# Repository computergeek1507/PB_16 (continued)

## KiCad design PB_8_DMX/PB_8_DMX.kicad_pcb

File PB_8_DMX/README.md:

# Copyright and Disclaimer
Copyright: Scott Hanson

This documentation describes Open Hardware and is licensed under the CERN Open Hardware License Version 2 - Strongly Reciprocal. (CERN-OHL-S)

You may redistribute and modify this documentation under the terms of the CERN OHL-S-v2 (https://ohwr.org/cern_ohl_s_v2.txt). This documentation is distributed WITHOUT ANY EXPRESS OR IMPLIED WARRANTY, INCLUDING OF MERCHANTABILITY, SATISFACTORY QUALITY AND FITNESS FOR A PARTICULAR PURPOSE. Please see the CERN OHL v2-S for applicable conditions

**Under CERN OHL-S-v2, derivative work must be publicly released as defined in subsection 3.3**

# PB 8 DMX

The PB 8 DMX Controller is designed as an open source DIY hobbyist controller. A Pocketbeagle running FPP drives the 8 serial ports. The design was made with all through hole components for easy assembly by most users. It is designed to be modular and support many use cases. It runs a full Linux operating system with ethernet, WIFI and audio supported over the USB port. It can run in standalone, or be used with other controllers/devices. It is 140mm (5’) wide by 103mm(4’) tall. The controllers small form factor and simplistic design are intended to limit overall cost. All the design files are open source and available on github. Open source applications were used to create this controller. [KiCad](http://kicad.org/) was used for the PCB design, and [LibreOffice](https://www.libreoffice.org/) for the documentation.

To order your own PCB upload the gerber.zip file to your favorite PCB manufacture of choice, I personally use [jlcpcb.com](https://jlcpcb.com/).

### Features
* Powered by FPP Falcon Player
* Standalone/Master/Remote/Bridge Support
* 8 DMX Serial Outputs
* USB port for Ethernet,WIFI, or Audio
* OLED Display header
* Adafruit Real Time Clock Header Connector
* 2 pin GPIO Header for Push Button or Relay Support
* 5v - 24v Vin Support

## [Gerbers](https://github.com/computergeek1507/PB_16/raw/master/jlcpcb/production_files/GERBER-PB_8_DMX.zip)

## [Interactive BOM](https://computergeek1507.github.io/PB_16/PB_8_DMX/bom/ibom)

---
## Changelog

v1
-
* 2023-09-24
* Initial Version.

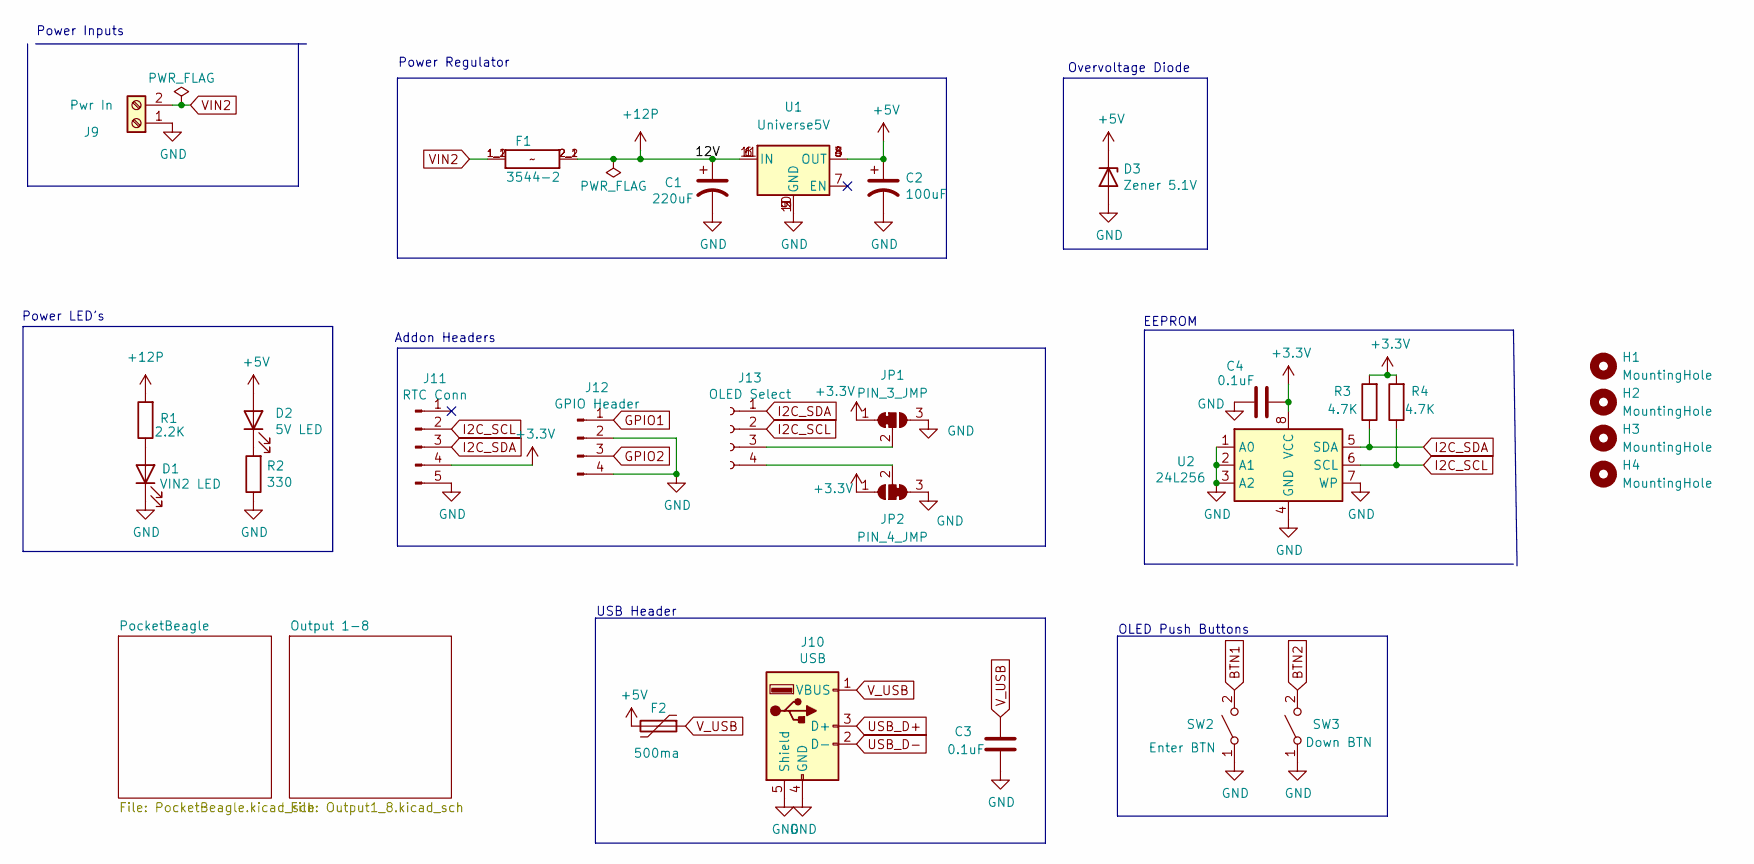
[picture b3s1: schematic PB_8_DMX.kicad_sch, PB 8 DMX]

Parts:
C1: 220uF; CP_Radial_D10.0mm_P5.00mm; MPN ECA-1HM221; Digi-Key_PN P5183-ND
C2: 100uF; CP_Radial_D5.0mm_P2.00mm; MPN 16ZLH100MEFC5X11; Digi-Key_PN 1189-1148-ND
C3, C4: 0.1uF; C_Rect_L7.0mm_W2.0mm_P5.00mm; MPN SR215C104KARTR1; Digi-Key_PN 478-7336-1-ND
D1: VIN2 LED; LED_D3.0mm_Clear; MPN WP3A8GD; Digi-Key_PN 754-1217-ND
D2: 5V LED; LED_D3.0mm_Clear; MPN WP3A8GD; Digi-Key_PN 754-1217-ND
D3: Zener 5.1V; D_5W_P10.16mm_Horizontal; MPN 1N5338BRLG; Digi-Key_PN 1N5338BRLGOSCT-ND
F1: 3544-2; FUSE_3544-2; MPN 3544-2; Digi-Key_PN 36-3544-2-ND
F2: 500ma; Fuse_BelFuse_0ZRE0005FF_L8.3mm_W3.8mm; MPN RXEF050-2; Digi-Key_PN RXEF050-2HFCT-ND
H1, H2, H3, H4: MountingHole; MountingHole_3.7mm
J9: Pwr In; TerminalBlock_Phoenix_MKDS-1,5-2_1x02_P5.00mm_Horizontal; MPN 1727010; Digi-Key_PN 277-1947-ND
J10: USB; USB_A_Molex_105057_Vertical; MPN 1050570001; Digi-Key_PN WM8672-ND
J11: RTC Conn; PinHeader_1x05_P2.54mm_Vertical; MPN 61300511121; Digi-Key_PN 732-5318-ND
J12: GPIO Header; JST_XH_B4B-XH-A_1x04_P2.50mm_Vertical; MPN B4B-XH-A(LF)(SN); Digi-Key_PN 455-2249-ND
J13: OLED Select; PinSocket_1x04_P2.54mm_Vertical; MPN PPTC041LFBN-RC; Digi-Key_PN S7002-ND
JP1: PIN_3_JMP; SolderJumper-3_P1mm_Bridged12
JP2: PIN_4_JMP; SolderJumper-3_P1mm_Bridged23
R1: 2.2K; R_Axial_DIN0207_L6.3mm_D2.5mm_P7.62mm_Horizontal; MPN CF14JT2K20; Digi-Key_PN CF14JT2K20CT-ND
R2: 330; R_Axial_DIN0207_L6.3mm_D2.5mm_P7.62mm_Horizontal; MPN CF14JT330R; Digi-Key_PN CF14JT330RCT-ND
R3, R4: 4.7K; R_Axial_DIN0207_L6.3mm_D2.5mm_P7.62mm_Horizontal; MPN CF14JT4K70; Digi-Key_PN CF14JT4K70CT-ND
SW2: Enter BTN; SW_PUSH_6mm; MPN 1825910-6; Digi-Key_PN 450-1650-ND
SW3: Down BTN; SW_PUSH_6mm; MPN 1825910-6; Digi-Key_PN 450-1650-ND
U1: Universe5V; Universal_5V_Horizontal; MPN OKI-78SR-5/1.5-W36-C; Digi-Key_PN 811-2196-5-ND
U2: 24L256; DIP-8_W7.62mm; MPN FT24C256A-UDR-B; Digi-Key_PN 1219-1052-ND

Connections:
+3.3V: C4.1, J11.4, JP1.1 (A), JP2.1 (A), R3.2, R4.2, U2.8 (VCC); also elsewhere on the board
+5V: C2.1, D2.2 (A), D3.1 (K), F2.2, U1.3 (OUT), U1.4 (OUT), U1.8 (OUT); also elsewhere on the board
+12P: C1.1, F1.2_1 (2), F1.2_2 (2), R1.2, U1.1 (IN), U1.6 (IN), U1.11 (IN)
BTN1: SW2.2 (B); also elsewhere on the board
BTN2: SW3.2 (B); also elsewhere on the board
GND: C1.2, C2.2, C3.2, C4.2, D1.1 (K), D3.2 (A), J9.1, J10.4 (GND), J10.5 (Shield), J11.5, J12.2, J12.4, JP1.3 (B), JP2.3 (B), R2.1, SW2.1 (A), SW3.1 (A), U1.2 (GND), U1.5 (GND), U1.9 (GND), U1.10 (GND), U2.1 (A0), U2.2 (A1), U2.3 (A2), U2.4 (GND), U2.7 (WP); also elsewhere on the board
GPIO1: J12.1; also elsewhere on the board
GPIO2: J12.3; also elsewhere on the board
I2C_SCL: J11.2, J13.2, R4.1, U2.6 (SCL); also elsewhere on the board
I2C_SDA: J11.3, J13.1, R3.1, U2.5 (SDA); also elsewhere on the board
unnamed: D1.2 (A), R1.1
unnamed: D2.1 (K), R2.2
unnamed: J13.3, JP1.2 (C)
unnamed: J13.4, JP2.2 (C)
USB_D+: J10.3 (D+); also elsewhere on the board
USB_D-: J10.2 (D-); also elsewhere on the board
VIN2: F1.1_1 (1), F1.1_2 (1), J9.2
V_USB: C3.1, F2.1, J10.1 (VBUS); also elsewhere on the board

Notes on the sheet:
Overvoltage Diode
EEPROM
USB Header
OLED Push Buttons
Addon Headers
Power Regulator
Power LED's
Power Inputs

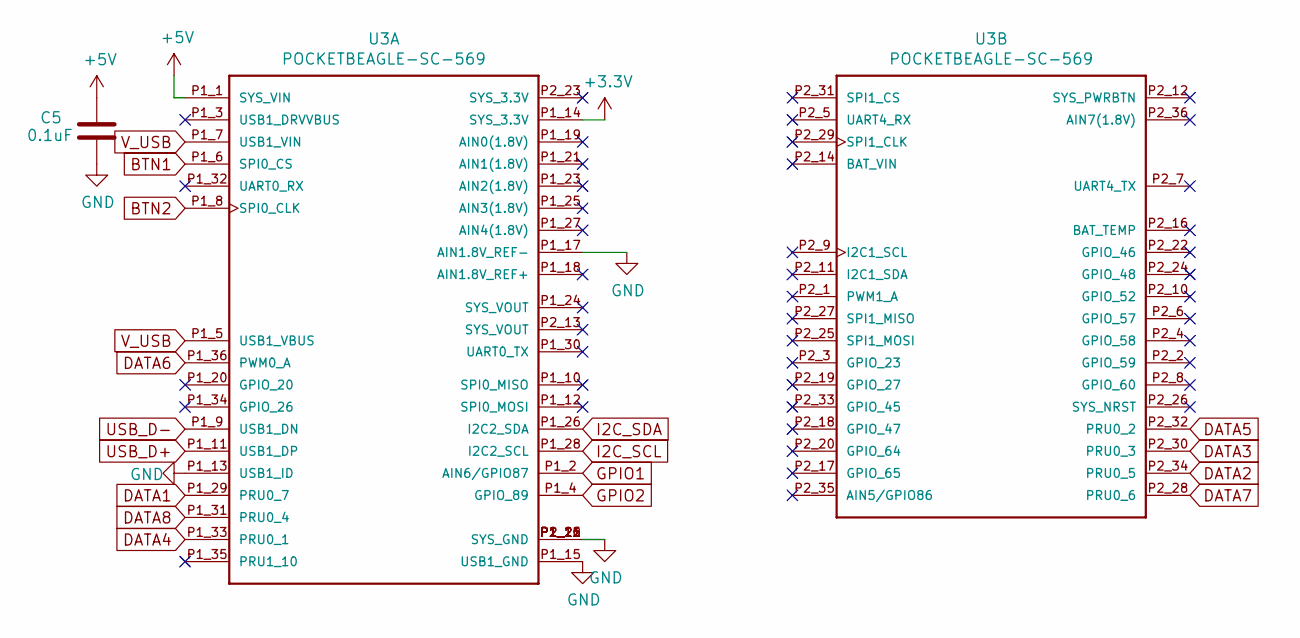
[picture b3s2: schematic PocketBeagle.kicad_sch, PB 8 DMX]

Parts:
C5: 0.1uF; C_Rect_L7.0mm_W2.0mm_P5.00mm; MPN SR215C104KARTR1; Digi-Key_PN 478-7336-1-ND
U3: POCKETBEAGLE-SC-569; BEAGLE_POCKETBEAGLE-SC-569; MPN POCKETBEAGLE-SC-569; Digi-Key_PN POCKETBEAGLE-SC-569-ND

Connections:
+3.3V: U3.P1_14 (SYS_3.3V); also elsewhere on the board
+5V: C5.1, U3.P1_1 (SYS_VIN); also elsewhere on the board
BTN1: U3.P1_6 (SPI0_CS); also elsewhere on the board
BTN2: U3.P1_8 (SPI0_CLK); also elsewhere on the board
DATA1: U3.P1_29 (PRU0_7); also elsewhere on the board
DATA2: U3.P2_34 (PRU0_5); also elsewhere on the board
DATA3: U3.P2_30 (PRU0_3); also elsewhere on the board
DATA4: U3.P1_33 (PRU0_1); also elsewhere on the board
DATA5: U3.P2_32 (PRU0_2); also elsewhere on the board
DATA6: U3.P1_36 (PWM0_A); also elsewhere on the board
DATA7: U3.P2_28 (PRU0_6); also elsewhere on the board
DATA8: U3.P1_31 (PRU0_4); also elsewhere on the board
GND: C5.2, U3.P1_13 (USB1_ID), U3.P1_15 (USB1_GND), U3.P1_16 (SYS_GND), U3.P1_17 (AIN1.8V_REF-), U3.P1_22 (SYS_GND), U3.P2_15 (SYS_GND), U3.P2_21 (SYS_GND); also elsewhere on the board
GPIO1: U3.P1_2 (AIN6/GPIO87); also elsewhere on the board
GPIO2: U3.P1_4 (GPIO_89); also elsewhere on the board
I2C_SCL: U3.P1_28 (I2C2_SCL); also elsewhere on the board
I2C_SDA: U3.P1_26 (I2C2_SDA); also elsewhere on the board
USB_D+: U3.P1_11 (USB1_DP); also elsewhere on the board
USB_D-: U3.P1_9 (USB1_DN); also elsewhere on the board
V_USB: U3.P1_5 (USB1_VBUS), U3.P1_7 (USB1_VIN); also elsewhere on the board

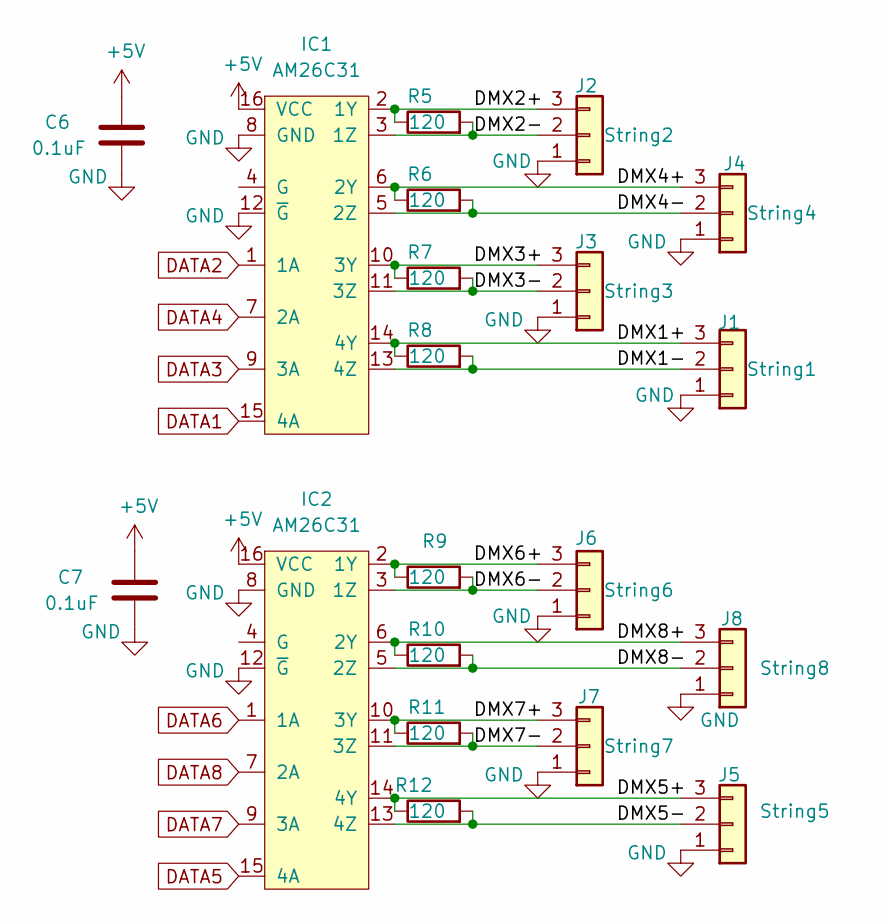
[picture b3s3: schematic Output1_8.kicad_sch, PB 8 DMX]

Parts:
C6, C7: 0.1uF; C_Rect_L7.0mm_W2.0mm_P5.00mm; MPN SR215C104KARTR1; Digi-Key_PN 478-7336-1-ND
IC1, IC2: AM26C31; DIP-16_W7.62mm; MPN 4975637; Farnell 4975637
J1: String1; PhoenixContact_MCV_1,5_3-G-3.5_1x03_P3.50mm_Vertical; MPN 1843619/OSTTJ0311530; Digi-Key_PN 277-5737-ND/ED10555-ND
J2: String2; PhoenixContact_MCV_1,5_3-G-3.5_1x03_P3.50mm_Vertical; MPN 1843619/OSTTJ0311530; Digi-Key_PN 277-5737-ND/ED10555-ND
J3: String3; PhoenixContact_MCV_1,5_3-G-3.5_1x03_P3.50mm_Vertical; MPN 1843619/OSTTJ0311530; Digi-Key_PN 277-5737-ND/ED10555-ND
J4: String4; PhoenixContact_MCV_1,5_3-G-3.5_1x03_P3.50mm_Vertical; MPN 1843619/OSTTJ0311530; Digi-Key_PN 277-5737-ND/ED10555-ND
J5: String5; PhoenixContact_MCV_1,5_3-G-3.5_1x03_P3.50mm_Vertical; MPN 1843619/OSTTJ0311530; Digi-Key_PN 277-5737-ND/ED10555-ND
J6: String6; PhoenixContact_MCV_1,5_3-G-3.5_1x03_P3.50mm_Vertical; MPN 1843619/OSTTJ0311530; Digi-Key_PN 277-5737-ND/ED10555-ND
J7: String7; PhoenixContact_MCV_1,5_3-G-3.5_1x03_P3.50mm_Vertical; MPN 1843619/OSTTJ0311530; Digi-Key_PN 277-5737-ND/ED10555-ND
J8: String8; PhoenixContact_MCV_1,5_3-G-3.5_1x03_P3.50mm_Vertical; MPN 1843619/OSTTJ0311530; Digi-Key_PN 277-5737-ND/ED10555-ND
R5, R6, R7, R8, R9, R10, R11, R12: 120; R_Axial_DIN0207_L6.3mm_D2.5mm_P7.62mm_Horizontal; MPN CF14JT120R; Digi-Key_PN CF14JT120RCT-ND

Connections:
+5V: C6.1, C7.1, IC1.16 (VCC), IC2.16 (VCC); also elsewhere on the board
/Output 1-8/DMX1+: IC1.14 (4Y), J1.3, R8.1
/Output 1-8/DMX1-: IC1.13 (4Z), J1.2, R8.2
/Output 1-8/DMX2+: IC1.2 (1Y), J2.3, R5.1
/Output 1-8/DMX2-: IC1.3 (1Z), J2.2, R5.2
/Output 1-8/DMX3+: IC1.10 (3Y), J3.3, R7.1
/Output 1-8/DMX3-: IC1.11 (3Z), J3.2, R7.2
/Output 1-8/DMX4+: IC1.6 (2Y), J4.3, R6.1
/Output 1-8/DMX4-: IC1.5 (2Z), J4.2, R6.2
/Output 1-8/DMX5+: IC2.14 (4Y), J5.3, R12.1
/Output 1-8/DMX5-: IC2.13 (4Z), J5.2, R12.2
/Output 1-8/DMX6+: IC2.2 (1Y), J6.3, R9.1
/Output 1-8/DMX6-: IC2.3 (1Z), J6.2, R9.2
/Output 1-8/DMX7+: IC2.10 (3Y), J7.3, R11.1
/Output 1-8/DMX7-: IC2.11 (3Z), J7.2, R11.2
/Output 1-8/DMX8+: IC2.6 (2Y), J8.3, R10.1
/Output 1-8/DMX8-: IC2.5 (2Z), J8.2, R10.2
DATA1: IC1.15 (4A); also elsewhere on the board
DATA2: IC1.1 (1A); also elsewhere on the board
DATA3: IC1.9 (3A); also elsewhere on the board
DATA4: IC1.7 (2A); also elsewhere on the board
DATA5: IC2.15 (4A); also elsewhere on the board
DATA6: IC2.1 (1A); also elsewhere on the board
DATA7: IC2.9 (3A); also elsewhere on the board
DATA8: IC2.7 (2A); also elsewhere on the board
GND: C6.2, C7.2, IC1.8 (GND), IC1.12 (~G), IC2.8 (GND), IC2.12 (~G), J1.1, J2.1, J3.1, J4.1, J5.1, J6.1, J7.1, J8.1; also elsewhere on the board

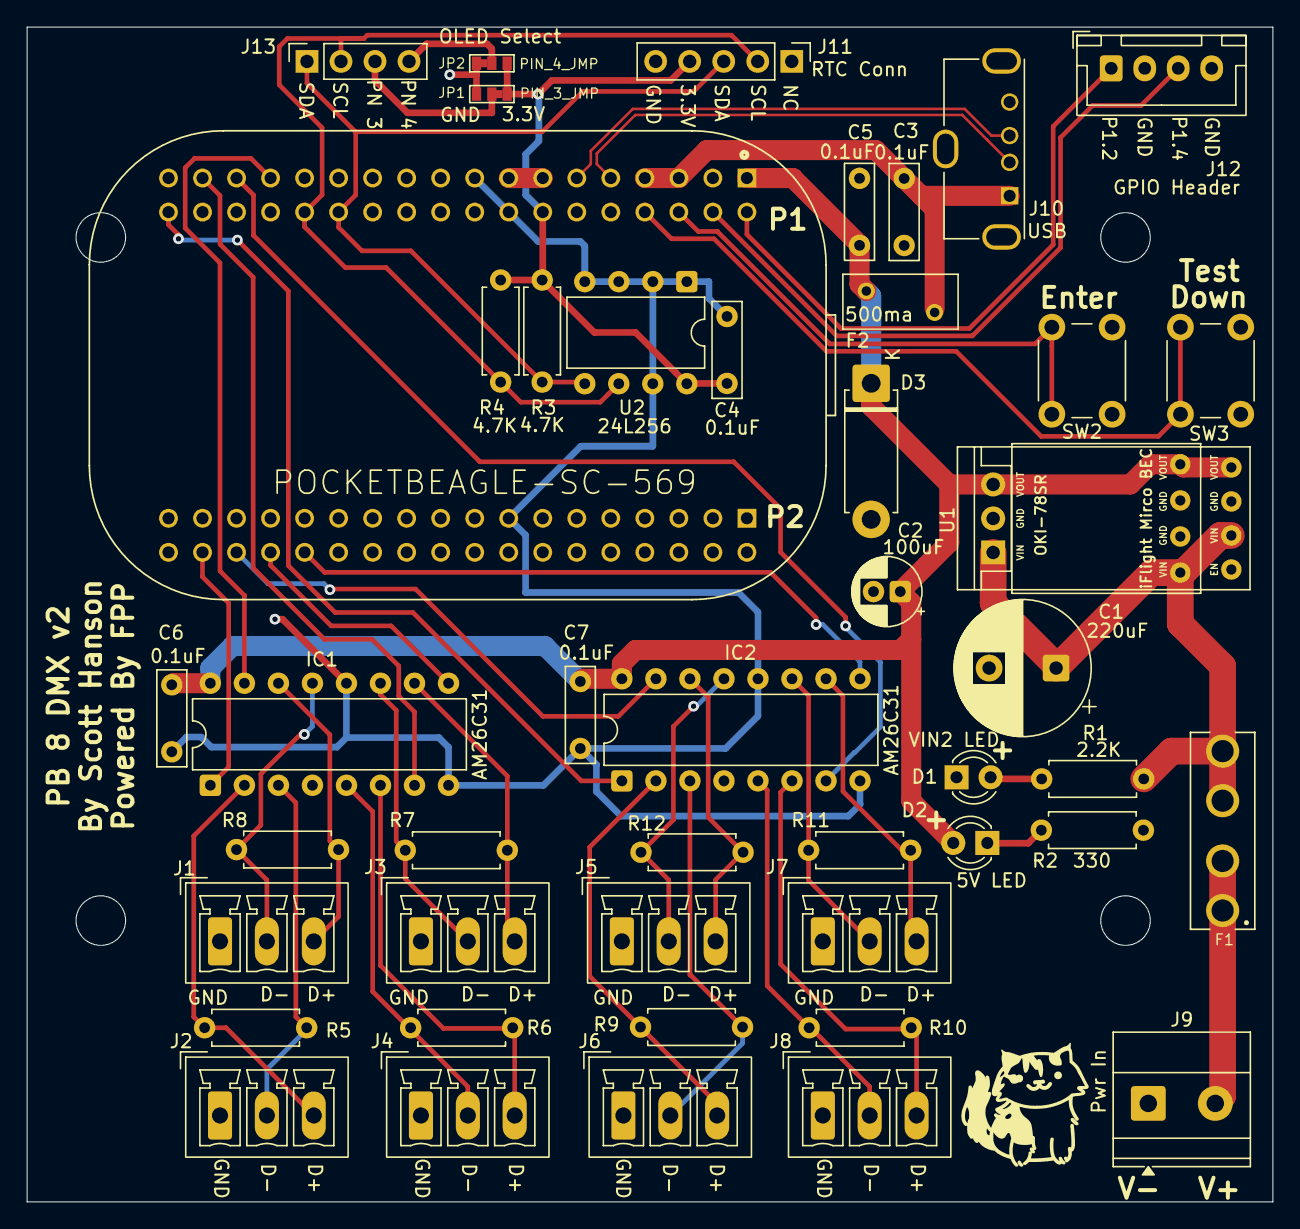
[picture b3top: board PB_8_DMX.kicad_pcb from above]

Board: 2 copper layers, 93.0 x 87.7 mm, 50 parts (0 on the bottom side), 42 nets.

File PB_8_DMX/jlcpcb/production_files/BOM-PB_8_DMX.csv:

Comment,Designator,Footprint,LCSC,Quantity
100uF,C2,CP_Radial_D5.0mm_P2.00mm,,1
0.1uF,C4,C_Rect_L7.0mm_W2.0mm_P5.00mm,,1
String2,J2,"PhoenixContact_MCV_1,5_3-G-3.5_1x03_P3.50mm_Vertical",,1
String5,J5,"PhoenixContact_MCV_1,5_3-G-3.5_1x03_P3.50mm_Vertical",,1
String6,J6,"PhoenixContact_MCV_1,5_3-G-3.5_1x03_P3.50mm_Vertical",,1
String7,J7,"PhoenixContact_MCV_1,5_3-G-3.5_1x03_P3.50mm_Vertical",,1
String8,J8,"PhoenixContact_MCV_1,5_3-G-3.5_1x03_P3.50mm_Vertical",,1
Pwr In,J9,"TerminalBlock_Phoenix_MKDS-1,5-2_1x02_P5.00mm_Horizontal",,1
USB,J10,USB_A_Molex_105057_Vertical,,1
RTC Conn,J11,PinHeader_1x05_P2.54mm_Vertical,,1
GPIO Header,J12,JST_XH_B4B-XH-A_1x04_P2.50mm_Vertical,,1
OLED Select,J13,PinSocket_1x04_P2.54mm_Vertical,,1
3544-2,F1,FUSE_3544-2,,1
5V LED,D2,LED_D3.0mm_Clear,,1
0.1uF,C3,C_Rect_L7.0mm_W2.0mm_P5.00mm,,1
500ma,F2,Fuse_BelFuse_0ZRE0005FF_L8.3mm_W3.8mm,,1
String1,J1,"PhoenixContact_MCV_1,5_3-G-3.5_1x03_P3.50mm_Vertical",,1
String3,J3,"PhoenixContact_MCV_1,5_3-G-3.5_1x03_P3.50mm_Vertical",,1
String4,J4,"PhoenixContact_MCV_1,5_3-G-3.5_1x03_P3.50mm_Vertical",,1
VIN2 LED,D1,LED_D3.0mm_Clear,,1
2.2K,R1,R_Axial_DIN0207_L6.3mm_D2.5mm_P7.62mm_Horizontal,,1
330,R2,R_Axial_DIN0207_L6.3mm_D2.5mm_P7.62mm_Horizontal,,1
24L256,U2,DIP-8_W7.62mm,,1
POCKETBEAGLE-SC-569,U3,BEAGLE_POCKETBEAGLE-SC-569,,1
0.1uF,C6,C_Rect_L7.0mm_W2.0mm_P5.00mm,,1
0.1uF,C7,C_Rect_L7.0mm_W2.0mm_P5.00mm,,1
Universe5V,U1,Universal_5V_Horizontal,,1
4.7K,R4,R_Axial_DIN0207_L6.3mm_D2.5mm_P7.62mm_Horizontal,,1
120,R5,R_Axial_DIN0207_L6.3mm_D2.5mm_P7.62mm_Horizontal,,1
4.7K,R3,R_Axial_DIN0207_L6.3mm_D2.5mm_P7.62mm_Horizontal,,1
Enter BTN,SW2,SW_PUSH_6mm,,1
220uF,C1,CP_Radial_D10.0mm_P5.00mm,,1
120,R6,R_Axial_DIN0207_L6.3mm_D2.5mm_P7.62mm_Horizontal,,1
120,R7,R_Axial_DIN0207_L6.3mm_D2.5mm_P7.62mm_Horizontal,,1
0.1uF,C5,C_Rect_L7.0mm_W2.0mm_P5.00mm,,1
Zener 5.1V,D3,D_5W_P10.16mm_Horizontal,,1
Down BTN,SW3,SW_PUSH_6mm,,1
AM26C31,IC2,DIP-16_W7.62mm,,1
120,R12,R_Axial_DIN0207_L6.3mm_D2.5mm_P7.62mm_Horizontal,,1
MountingHole,H4,MountingHole_3.7mm,,1
MountingHole,H1,MountingHole_3.7mm,,1
120,R11,R_Axial_DIN0207_L6.3mm_D2.5mm_P7.62mm_Horizontal,,1
120,R8,R_Axial_DIN0207_L6.3mm_D2.5mm_P7.62mm_Horizontal,,1
120,R9,R_Axial_DIN0207_L6.3mm_D2.5mm_P7.62mm_Horizontal,,1
120,R10,R_Axial_DIN0207_L6.3mm_D2.5mm_P7.62mm_Horizontal,,1
MountingHole,H2,MountingHole_3.7mm,,1
AM26C31,IC1,DIP-16_W7.62mm,,1
MountingHole,H3,MountingHole_3.7mm,,1

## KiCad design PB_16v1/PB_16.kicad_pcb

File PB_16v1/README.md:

# Copyright and Disclaimer
Copyright: Scott Hanson

This documentation describes Open Hardware and is licensed under the CERN Open Hardware License Version 2 - Strongly Reciprocal. (CERN-OHL-S)

You may redistribute and modify this documentation under the terms of the CERN OHL-S-v2 (https://ohwr.org/cern_ohl_s_v2.txt). This documentation is distributed WITHOUT ANY EXPRESS OR IMPLIED WARRANTY, INCLUDING OF MERCHANTABILITY, SATISFACTORY QUALITY AND FITNESS FOR A PARTICULAR PURPOSE. Please see the CERN OHL v2-S for applicable conditions

**Under CERN OHL-S-v2, derivative work must be publicly released as defined in subsection 3.3**

# PB 16

The PB16 Pixel Controller is designed as an open source DIY hobbyist controller. A Pocketbeagle running FPP drives the 16 pixel ports and 2 serial ports. The design was made with all through hole components for easy assembly by most users. It is designed to be modular and support many use cases. It runs a full Linux operating system with ethernet, WIFI and audio supported over the USB port. It can run in standalone, or be used with other controllers/devices. It is 140mm (5’) wide by 103mm(4’) tall. The controllers small form factor and simplistic design are intended to limit overall cost. All the design files are open source and available on github. Open source applications were used to create this controller. [KiCad](http://kicad.org/) was used for the PCB design, and [LibreOffice](https://www.libreoffice.org/) for the documentation.

To order your own PCB upload the gerber.zip file to your favorite PCB manufacture of choice, I personally use [jlcpcb.com](https://jlcpcb.com/).

Assembly Instructions are included in the manual below.

### Features
* Powered by FPP Falcon Player
* Standalone/Master/Remote/Bridge Support
* 16 3-Wire Pixel Ports
* 700 pixel per output at 40 FPS or 1300 at 20 FPS
* 2 DMX Serial Outputs
* 2 RJ-45 Connectors with DMX/LOR/Renard Wiring Support
* Fused Powered DMX Output
* USB port for Ethernet,WIFI, or Audio
* OLED Display header
* Adafruit Real Time Clock Header Connector
* 2 pin GPIO Header for Push Button or Relay Support
* 5v - 24v Vin Support
* Expansion Header for additional 16 pixel outputs, Supports Falcon(v3) Expansion Boards

## [Manual](https://github.com/computergeek1507/PB_16/raw/master/PB_16v1/FPP%20PB16%20Pixel%20Controller%20Manual%20and%20Assembly%20Guide.pdf)

## [Gerbers](https://github.com/computergeek1507/PB_16/raw/master/PB_16v1/gerbers/gerbers.zip)

## [Part BOM](https://github.com/computergeek1507/PB_16/raw/master/PB_16v1/PB16_Bom.ods)

## [Interactive BOM](https://computergeek1507.github.io/PB_16/PB_16v1/bom/ibom)

## [Ordering Instructions](https://github.com/computergeek1507/PB_16/blob/master/JLC_PCB.md)

---
## Changelog

v1 rev I 
- 
* 2026-03-06
* Switched Expansion Header to 24pin Falcon V4 pinout.
* Removed OLED Slide Switch.

v1 rev H 
- 
* 2022-05-29
* Updated 5V regulator to "Universal" footprint to support different regulators.
* Added Chewi Logo.

v1 rev G 
-
* 2020-05-09
* Moved to barrier block screws connectors for Power Inputs.
* Fix AUX power pin holes too small.

v1 rev F
-
* 2019-10-07
* Added Serial Selector for LOR/DMX, EEPROM, Push Buttons.

v1 rev E
-
* 2019-09-19
* Increased AUX power input terminal footprint to 3.81mm. (Pin Holes were too small)

v1 rev D
-
* 2019-08-24
* Added OLED wiring selector switch and AUX power input.

v1 rev C
-
* 2019-08-12
* Added LEDs and GPIO Header. (First functional PCBs)

v1 rev B(v1.1)
-
* 2019-07-31
* Added Expansion, DMX2 RJ45, and OLED Headers. (non-functioning due to wiring issues)

v1 rev A(v1.0)
-
* 2019-06-19(SEH B-Day)
* Initial Version. (First non-functioning Prototype PCBs)

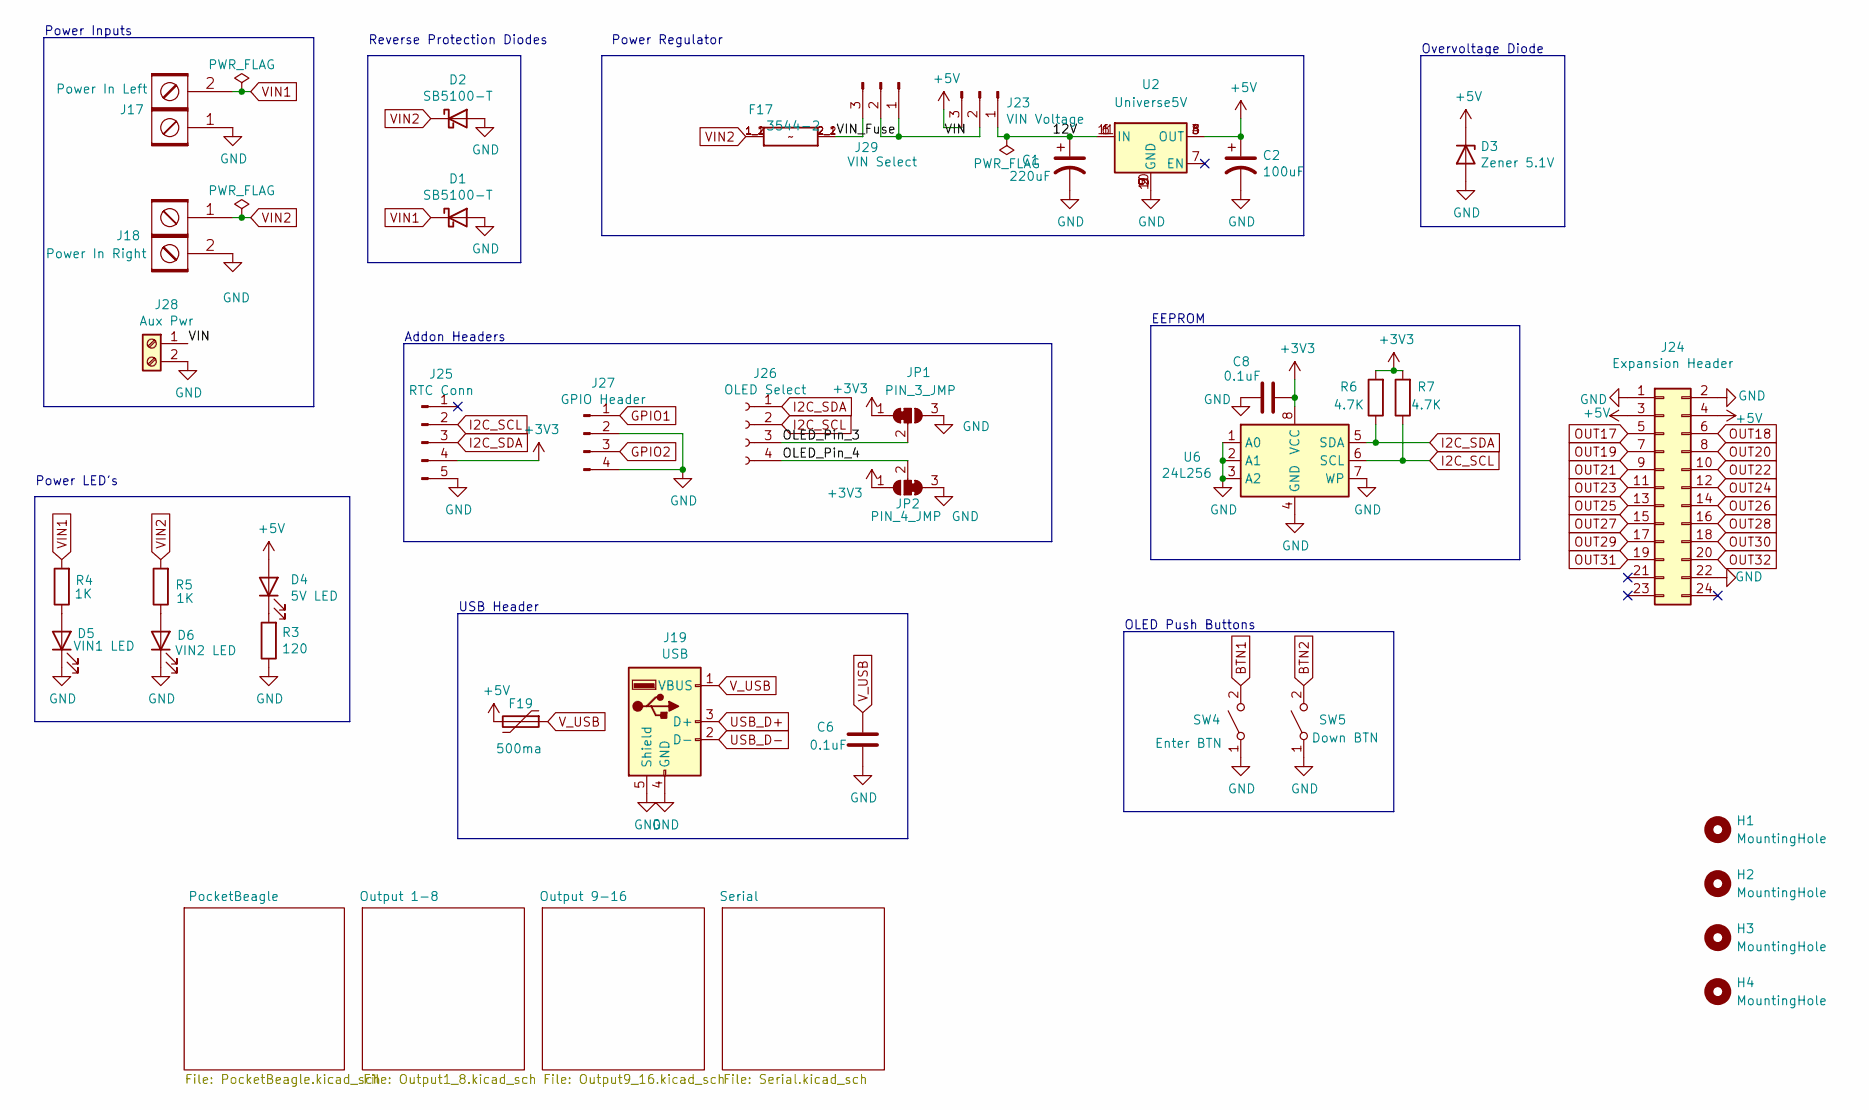
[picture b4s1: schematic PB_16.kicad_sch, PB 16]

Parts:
C1: 220uF; CP_Radial_D10.0mm_P5.00mm; MPN ECA-1HM221; Digi-Key_PN P5183-ND
C2: 100uF; CP_Radial_D5.0mm_P2.00mm; MPN 16ZLH100MEFC5X11; Digi-Key_PN 1189-1148-ND
C6, C8: 0.1uF; C_Rect_L7.0mm_W2.0mm_P5.00mm; MPN SR215C104KARTR1; Digi-Key_PN 478-7336-1-ND
D1, D2: SB5100-T; D_DO-201AD_P12.70mm_Horizontal; MPN SB5100-T; Digi-Key_PN SB5100DICT-ND
D3: Zener 5.1V; D_5W_P10.16mm_Horizontal; MPN 1N5338BRLG; Digi-Key_PN 1N5338BRLGOSCT-ND
D4: 5V LED; LED_D3.0mm_Clear; MPN WP3A8GD; Digi-Key_PN 754-1217-ND
D5: VIN1 LED; LED_D3.0mm_Clear; MPN WP3A8GD; Digi-Key_PN 754-1217-ND
D6: VIN2 LED; LED_D3.0mm_Clear; MPN WP3A8GD; Digi-Key_PN 754-1217-ND
F17: 3544-2; FUSE_3544-2; MPN 3544-2; Digi-Key_PN 36-3544-2-ND
F19: 500ma; Fuse_BelFuse_0ZRE0005FF_L8.3mm_W3.8mm; MPN RXEF050-2; Digi-Key_PN RXEF050-2HFCT-ND
H1, H2, H3, H4: MountingHole; MountingHole_3.7mm
J17: Power In Left; BARRIER_BLOCK_1ROW_2POS_P9.5MM; MPN OSTYK51102030; Digi-Key_PN ED2953-ND
J18: Power In Right; BARRIER_BLOCK_1ROW_2POS_P9.5MM; MPN OSTYK51102030; Digi-Key_PN ED2953-ND
J19: USB; USB_A_Molex_105057_Vertical; MPN 1050570001; Digi-Key_PN WM8672-ND
J23: VIN Voltage; PinHeader_1x03_P2.54mm_Vertical; MPN 61300311121; Digi-Key_PN 732-5316-ND
J24: Expansion Header; IDC-Header_2x12_P2.54mm_Vertical; MPN SBH11-PBPC-D20-ST-BK; Digi-Key_PN S9175-ND
J25: RTC Conn; PinHeader_1x05_P2.54mm_Vertical; MPN 61300511121; Digi-Key_PN 732-5318-ND
J26: OLED Select; PinSocket_1x04_P2.54mm_Vertical; MPN PPTC041LFBN-RC; Digi-Key_PN S7002-ND
J27: GPIO Header; JST_XH_B4B-XH-A_1x04_P2.50mm_Vertical; MPN B4B-XH-A(LF)(SN); Digi-Key_PN 455-2249-ND
J28: Aux Pwr; PHOENIX_MKDS1_2-3.81; MPN 1727010; Digi-Key_PN 277-1947-ND
J29: VIN Select; PinHeader_1x03_P2.54mm_Vertical; MPN 61300311121; Digi-Key_PN 732-5316-ND
JP1: PIN_3_JMP; SolderJumper-3_P1mm_Bridged12
JP2: PIN_4_JMP; SolderJumper-3_P1mm_Bridged23
R3: 120; R_Axial_DIN0207_L6.3mm_D2.5mm_P7.62mm_Horizontal; MPN CF14JT120R; Digi-Key_PN CF14JT120RCT-ND
R4, R5: 1K; R_Axial_DIN0207_L6.3mm_D2.5mm_P7.62mm_Horizontal; MPN CF14JT1K00; Digi-Key_PN CF14JT1K00CT-ND
R6, R7: 4.7K; R_Axial_DIN0207_L6.3mm_D2.5mm_P7.62mm_Horizontal; MPN CF14JT4K70; Digi-Key_PN CF14JT4K70CT-ND
SW4: Enter BTN; SW_PUSH_6mm; MPN 1825910-6; Digi-Key_PN 450-1650-ND
SW5: Down BTN; SW_PUSH_6mm; MPN 1825910-6; Digi-Key_PN 450-1650-ND
U2: Universe5V; Universal_5V_Horizontal
U6: 24L256; DIP-8_W7.62mm; MPN FT24C256A-UDR-B; Digi-Key_PN 1219-1052-ND

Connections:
+3V3: C8.1, J25.4, JP1.1 (A), JP2.1 (A), R6.2, R7.2, U6.8 (VCC); also elsewhere on the board
+5V: C2.1, D3.1 (K), D4.2 (A), F19.2, J23.3, J24.3, J24.4, U2.3 (OUT), U2.4 (OUT), U2.8 (OUT); also elsewhere on the board
/12V: C1.1, J23.1, U2.1 (IN), U2.6 (IN), U2.11 (IN)
/OLED_Pin_3: J26.3, JP1.2 (C)
/OLED_Pin_4: J26.4, JP2.2 (C)
/VIN: J23.2, J28.1, J29.1, J29.2
/VIN_Fuse: F17.2_1 (2), F17.2_2 (2), J29.3
BTN1: SW4.2 (B); also elsewhere on the board
BTN2: SW5.2 (B); also elsewhere on the board
GND: C1.2, C2.2, C6.2, C8.2, D1.2 (A), D2.2 (A), D3.2 (A), D5.1 (K), D6.1 (K), J17.1, J18.2, J19.4 (GND), J19.5 (Shield), J24.1, J24.2, J24.22, J25.5, J27.2, J27.4, J28.2, JP1.3 (B), JP2.3 (B), R3.1, SW4.1 (A), SW5.1 (A), U2.2 (GND), U2.5 (GND), U2.9 (GND), U2.10 (GND), U6.1 (A0), U6.2 (A1), U6.3 (A2), U6.4 (GND), U6.7 (WP); also elsewhere on the board
GPIO1: J27.1; also elsewhere on the board
GPIO2: J27.3; also elsewhere on the board
I2C_SCL: J25.2, J26.2, R7.1, U6.6 (SCL); also elsewhere on the board
I2C_SDA: J25.3, J26.1, R6.1, U6.5 (SDA); also elsewhere on the board
unnamed: D4.1 (K), R3.2
unnamed: D5.2 (A), R4.1
unnamed: D6.2 (A), R5.1
OUT17: J24.5; also elsewhere on the board
OUT18: J24.6; also elsewhere on the board
OUT19: J24.7; also elsewhere on the board
OUT20: J24.8; also elsewhere on the board
OUT21: J24.9; also elsewhere on the board
OUT22: J24.10; also elsewhere on the board
OUT23: J24.11; also elsewhere on the board
OUT24: J24.12; also elsewhere on the board
OUT25: J24.13; also elsewhere on the board
OUT26: J24.14; also elsewhere on the board
OUT27: J24.15; also elsewhere on the board
OUT28: J24.16; also elsewhere on the board
OUT29: J24.17; also elsewhere on the board
OUT30: J24.18; also elsewhere on the board
OUT31: J24.19; also elsewhere on the board
OUT32: J24.20; also elsewhere on the board
USB_D+: J19.3 (D+); also elsewhere on the board
USB_D-: J19.2 (D-); also elsewhere on the board
VIN1: D1.1 (K), J17.2, R4.2; also elsewhere on the board
VIN2: D2.1 (K), F17.1_1 (1), F17.1_2 (1), J18.1, R5.2; also elsewhere on the board
V_USB: C6.1, F19.1, J19.1 (VBUS); also elsewhere on the board

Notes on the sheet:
Overvoltage Diode
EEPROM
USB Header
OLED Push Buttons
Reverse Protection Diodes
Addon Headers
Power Regulator
Power LED's
Power Inputs

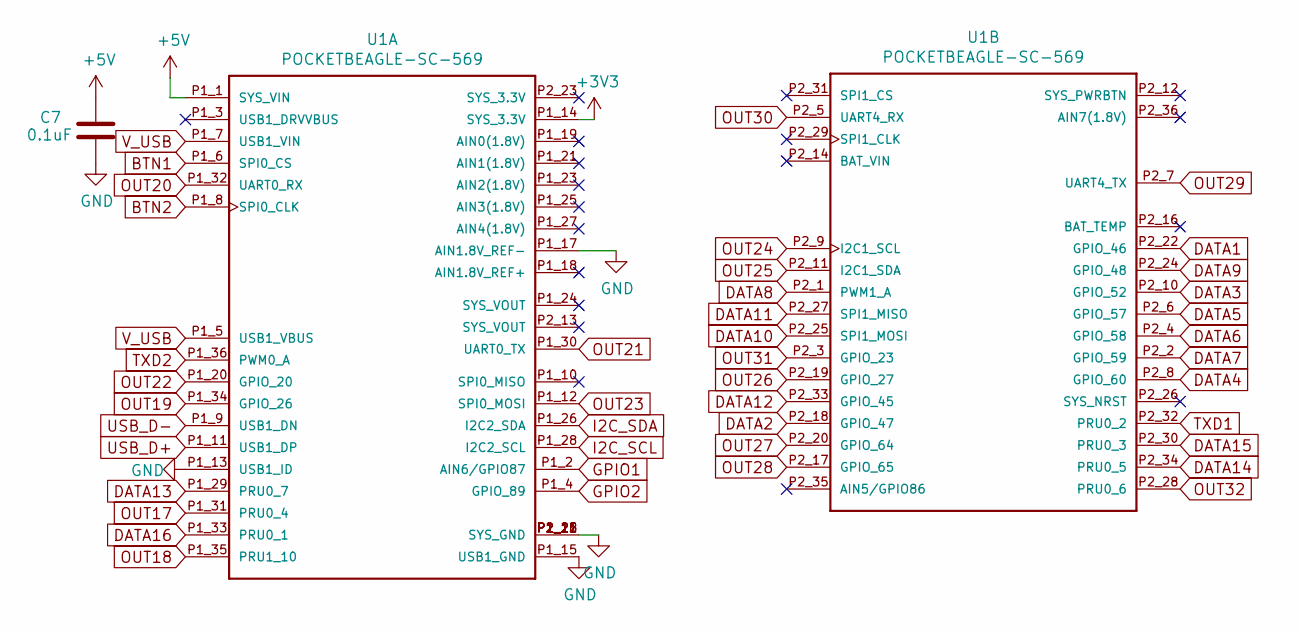
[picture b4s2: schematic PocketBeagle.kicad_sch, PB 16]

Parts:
C7: 0.1uF; C_Rect_L7.0mm_W2.0mm_P5.00mm; MPN SR215C104KARTR1; Digi-Key_PN 478-7336-1-ND
U1: POCKETBEAGLE-SC-569; BEAGLE_POCKETBEAGLE-SC-569; MPN POCKETBEAGLE-SC-569; Digi-Key_PN POCKETBEAGLE-SC-569-ND

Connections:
+3V3: U1.P1_14 (SYS_3.3V); also elsewhere on the board
+5V: C7.1, U1.P1_1 (SYS_VIN); also elsewhere on the board
BTN1: U1.P1_6 (SPI0_CS); also elsewhere on the board
BTN2: U1.P1_8 (SPI0_CLK); also elsewhere on the board
DATA1: U1.P2_22 (GPIO_46); also elsewhere on the board
DATA2: U1.P2_18 (GPIO_47); also elsewhere on the board
DATA3: U1.P2_10 (GPIO_52); also elsewhere on the board
DATA4: U1.P2_8 (GPIO_60); also elsewhere on the board
DATA5: U1.P2_6 (GPIO_57); also elsewhere on the board
DATA6: U1.P2_4 (GPIO_58); also elsewhere on the board
DATA7: U1.P2_2 (GPIO_59); also elsewhere on the board
DATA8: U1.P2_1 (PWM1_A); also elsewhere on the board
DATA9: U1.P2_24 (GPIO_48); also elsewhere on the board
DATA10: U1.P2_25 (SPI1_MOSI); also elsewhere on the board
DATA11: U1.P2_27 (SPI1_MISO); also elsewhere on the board
DATA12: U1.P2_33 (GPIO_45); also elsewhere on the board
DATA13: U1.P1_29 (PRU0_7); also elsewhere on the board
DATA14: U1.P2_34 (PRU0_5); also elsewhere on the board
DATA15: U1.P2_30 (PRU0_3); also elsewhere on the board
DATA16: U1.P1_33 (PRU0_1); also elsewhere on the board
GND: C7.2, U1.P1_13 (USB1_ID), U1.P1_15 (USB1_GND), U1.P1_16 (SYS_GND), U1.P1_17 (AIN1.8V_REF-), U1.P1_22 (SYS_GND), U1.P2_15 (SYS_GND), U1.P2_21 (SYS_GND); also elsewhere on the board
GPIO1: U1.P1_2 (AIN6/GPIO87); also elsewhere on the board
GPIO2: U1.P1_4 (GPIO_89); also elsewhere on the board
I2C_SCL: U1.P1_28 (I2C2_SCL); also elsewhere on the board
I2C_SDA: U1.P1_26 (I2C2_SDA); also elsewhere on the board
OUT17: U1.P1_31 (PRU0_4); also elsewhere on the board
OUT18: U1.P1_35 (PRU1_10); also elsewhere on the board
OUT19: U1.P1_34 (GPIO_26); also elsewhere on the board
OUT20: U1.P1_32 (UART0_RX); also elsewhere on the board
OUT21: U1.P1_30 (UART0_TX); also elsewhere on the board
OUT22: U1.P1_20 (GPIO_20); also elsewhere on the board
OUT23: U1.P1_12 (SPI0_MOSI); also elsewhere on the board
OUT24: U1.P2_9 (I2C1_SCL); also elsewhere on the board
OUT25: U1.P2_11 (I2C1_SDA); also elsewhere on the board
OUT26: U1.P2_19 (GPIO_27); also elsewhere on the board
OUT27: U1.P2_20 (GPIO_64); also elsewhere on the board
OUT28: U1.P2_17 (GPIO_65); also elsewhere on the board
OUT29: U1.P2_7 (UART4_TX); also elsewhere on the board
OUT30: U1.P2_5 (UART4_RX); also elsewhere on the board
OUT31: U1.P2_3 (GPIO_23); also elsewhere on the board
OUT32: U1.P2_28 (PRU0_6); also elsewhere on the board
TXD1: U1.P2_32 (PRU0_2); also elsewhere on the board
TXD2: U1.P1_36 (PWM0_A); also elsewhere on the board
USB_D+: U1.P1_11 (USB1_DP); also elsewhere on the board
USB_D-: U1.P1_9 (USB1_DN); also elsewhere on the board
V_USB: U1.P1_5 (USB1_VBUS), U1.P1_7 (USB1_VIN); also elsewhere on the board

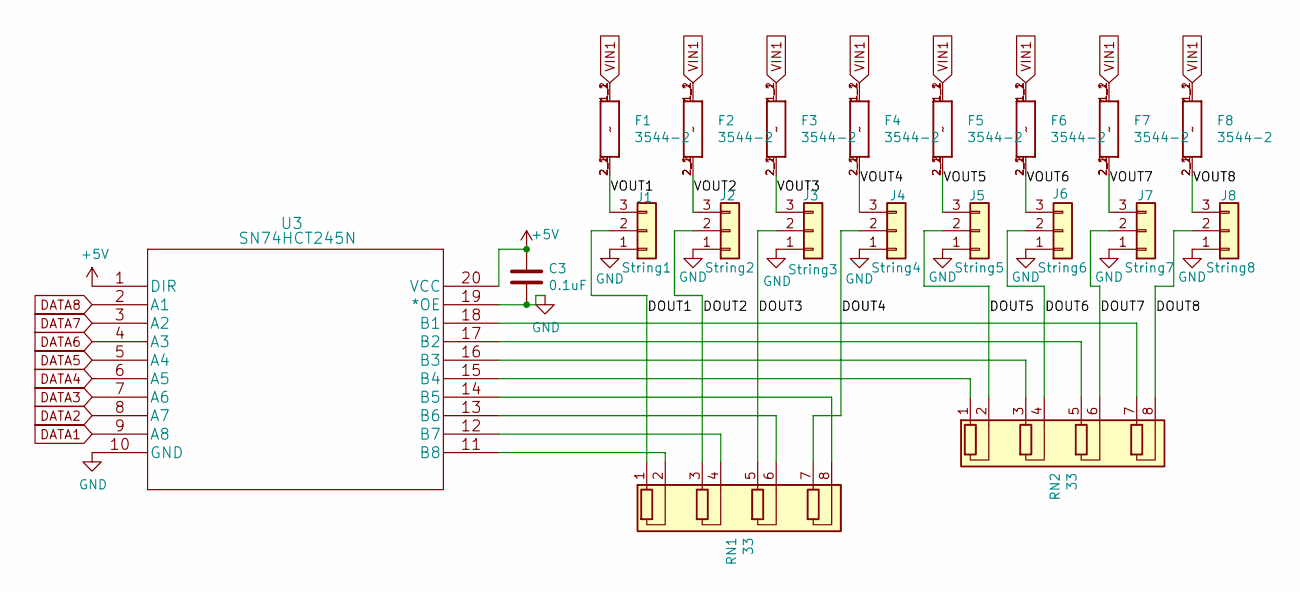
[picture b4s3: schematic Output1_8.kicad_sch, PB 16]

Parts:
C3: 0.1uF; C_Rect_L7.0mm_W2.0mm_P5.00mm; MPN SR215C104KARTR1; Digi-Key_PN 478-7336-1-ND
F1, F2, F3, F4, F5, F6, F7, F8: 3544-2; FUSE_3544-2; MPN 3544-2; Digi-Key_PN 36-3544-2-ND
J1: String1; PhoenixContact_MCV_1,5_3-G-3.5_1x03_P3.50mm_Vertical; MPN 1843619/OSTTJ0311530; Digi-Key_PN 277-5737-ND/ED10555-ND
J2: String2; PhoenixContact_MCV_1,5_3-G-3.5_1x03_P3.50mm_Vertical; MPN 1843619/OSTTJ0311530; Digi-Key_PN 277-5737-ND/ED10555-ND
J3: String3; PhoenixContact_MCV_1,5_3-G-3.5_1x03_P3.50mm_Vertical; MPN 1843619/OSTTJ0311530; Digi-Key_PN 277-5737-ND/ED10555-ND
J4: String4; PhoenixContact_MCV_1,5_3-G-3.5_1x03_P3.50mm_Vertical; MPN 1843619/OSTTJ0311530; Digi-Key_PN 277-5737-ND/ED10555-ND
J5: String5; PhoenixContact_MCV_1,5_3-G-3.5_1x03_P3.50mm_Vertical; MPN 1843619/OSTTJ0311530; Digi-Key_PN 277-5737-ND/ED10555-ND
J6: String6; PhoenixContact_MCV_1,5_3-G-3.5_1x03_P3.50mm_Vertical; MPN 1843619/OSTTJ0311530; Digi-Key_PN 277-5737-ND/ED10555-ND
J7: String7; PhoenixContact_MCV_1,5_3-G-3.5_1x03_P3.50mm_Vertical; MPN 1843619/OSTTJ0311530; Digi-Key_PN 277-5737-ND/ED10555-ND
J8: String8; PhoenixContact_MCV_1,5_3-G-3.5_1x03_P3.50mm_Vertical; MPN 1843619/OSTTJ0311530; Digi-Key_PN 277-5737-ND/ED10555-ND
RN1, RN2: 33; R_Array_SIP8; MPN 4608X-102-330LF; Digi-Key_PN 4608X-2-330LF-ND
U3: SN74HCT245N; MPN SN74HCT245N; Digi-Key_PN 296-1612-5-ND

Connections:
+5V: C3.1, U3.1 (DIR), U3.20 (VCC); also elsewhere on the board
/Output 1-8/DOUT1: J1.2, RN1.1 (R1.1)
/Output 1-8/DOUT2: J2.2, RN1.3 (R2.1)
/Output 1-8/DOUT3: J3.2, RN1.5 (R3.1)
/Output 1-8/DOUT4: J4.2, RN1.7 (R4.1)
/Output 1-8/DOUT5: J5.2, RN2.2 (R1.2)
/Output 1-8/DOUT6: J6.2, RN2.4 (R2.2)
/Output 1-8/DOUT7: J7.2, RN2.6 (R3.2)
/Output 1-8/DOUT8: J8.2, RN2.8 (R4.2)
/Output 1-8/VOUT1: F1.2_1 (2), F1.2_2 (2), J1.3
/Output 1-8/VOUT2: F2.2_1 (2), F2.2_2 (2), J2.3
/Output 1-8/VOUT3: F3.2_1 (2), F3.2_2 (2), J3.3
/Output 1-8/VOUT4: F4.2_1 (2), F4.2_2 (2), J4.3
/Output 1-8/VOUT5: F5.2_1 (2), F5.2_2 (2), J5.3
/Output 1-8/VOUT6: F6.2_1 (2), F6.2_2 (2), J6.3
/Output 1-8/VOUT7: F7.2_1 (2), F7.2_2 (2), J7.3
/Output 1-8/VOUT8: F8.2_1 (2), F8.2_2 (2), J8.3
DATA1: U3.9 (A8); also elsewhere on the board
DATA2: U3.8 (A7); also elsewhere on the board
DATA3: U3.7 (A6); also elsewhere on the board
DATA4: U3.6 (A5); also elsewhere on the board
DATA5: U3.5 (A4); also elsewhere on the board
DATA6: U3.4 (A3); also elsewhere on the board
DATA7: U3.3 (A2); also elsewhere on the board
DATA8: U3.2 (A1); also elsewhere on the board
GND: C3.2, J1.1, J2.1, J3.1, J4.1, J5.1, J6.1, J7.1, J8.1, U3.10 (GND), U3.19 (*OE); also elsewhere on the board
unnamed: RN1.2 (R1.2), U3.11 (B8)
unnamed: RN1.4 (R2.2), U3.12 (B7)
unnamed: RN1.6 (R3.2), U3.13 (B6)
unnamed: RN1.8 (R4.2), U3.14 (B5)
unnamed: RN2.1 (R1.1), U3.15 (B4)
unnamed: RN2.3 (R2.1), U3.16 (B3)
unnamed: RN2.5 (R3.1), U3.17 (B2)
unnamed: RN2.7 (R4.1), U3.18 (B1)
VIN1: F1.1_1 (1), F1.1_2 (1), F2.1_1 (1), F2.1_2 (1), F3.1_1 (1), F3.1_2 (1), F4.1_1 (1), F4.1_2 (1), F5.1_1 (1), F5.1_2 (1), F6.1_1 (1), F6.1_2 (1), F7.1_1 (1), F7.1_2 (1), F8.1_1 (1), F8.1_2 (1); also elsewhere on the board
